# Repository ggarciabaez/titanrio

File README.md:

# titanrio
A RoboRIO-Inspired Expansion board for Robotics. Mostly for funsies + learning.

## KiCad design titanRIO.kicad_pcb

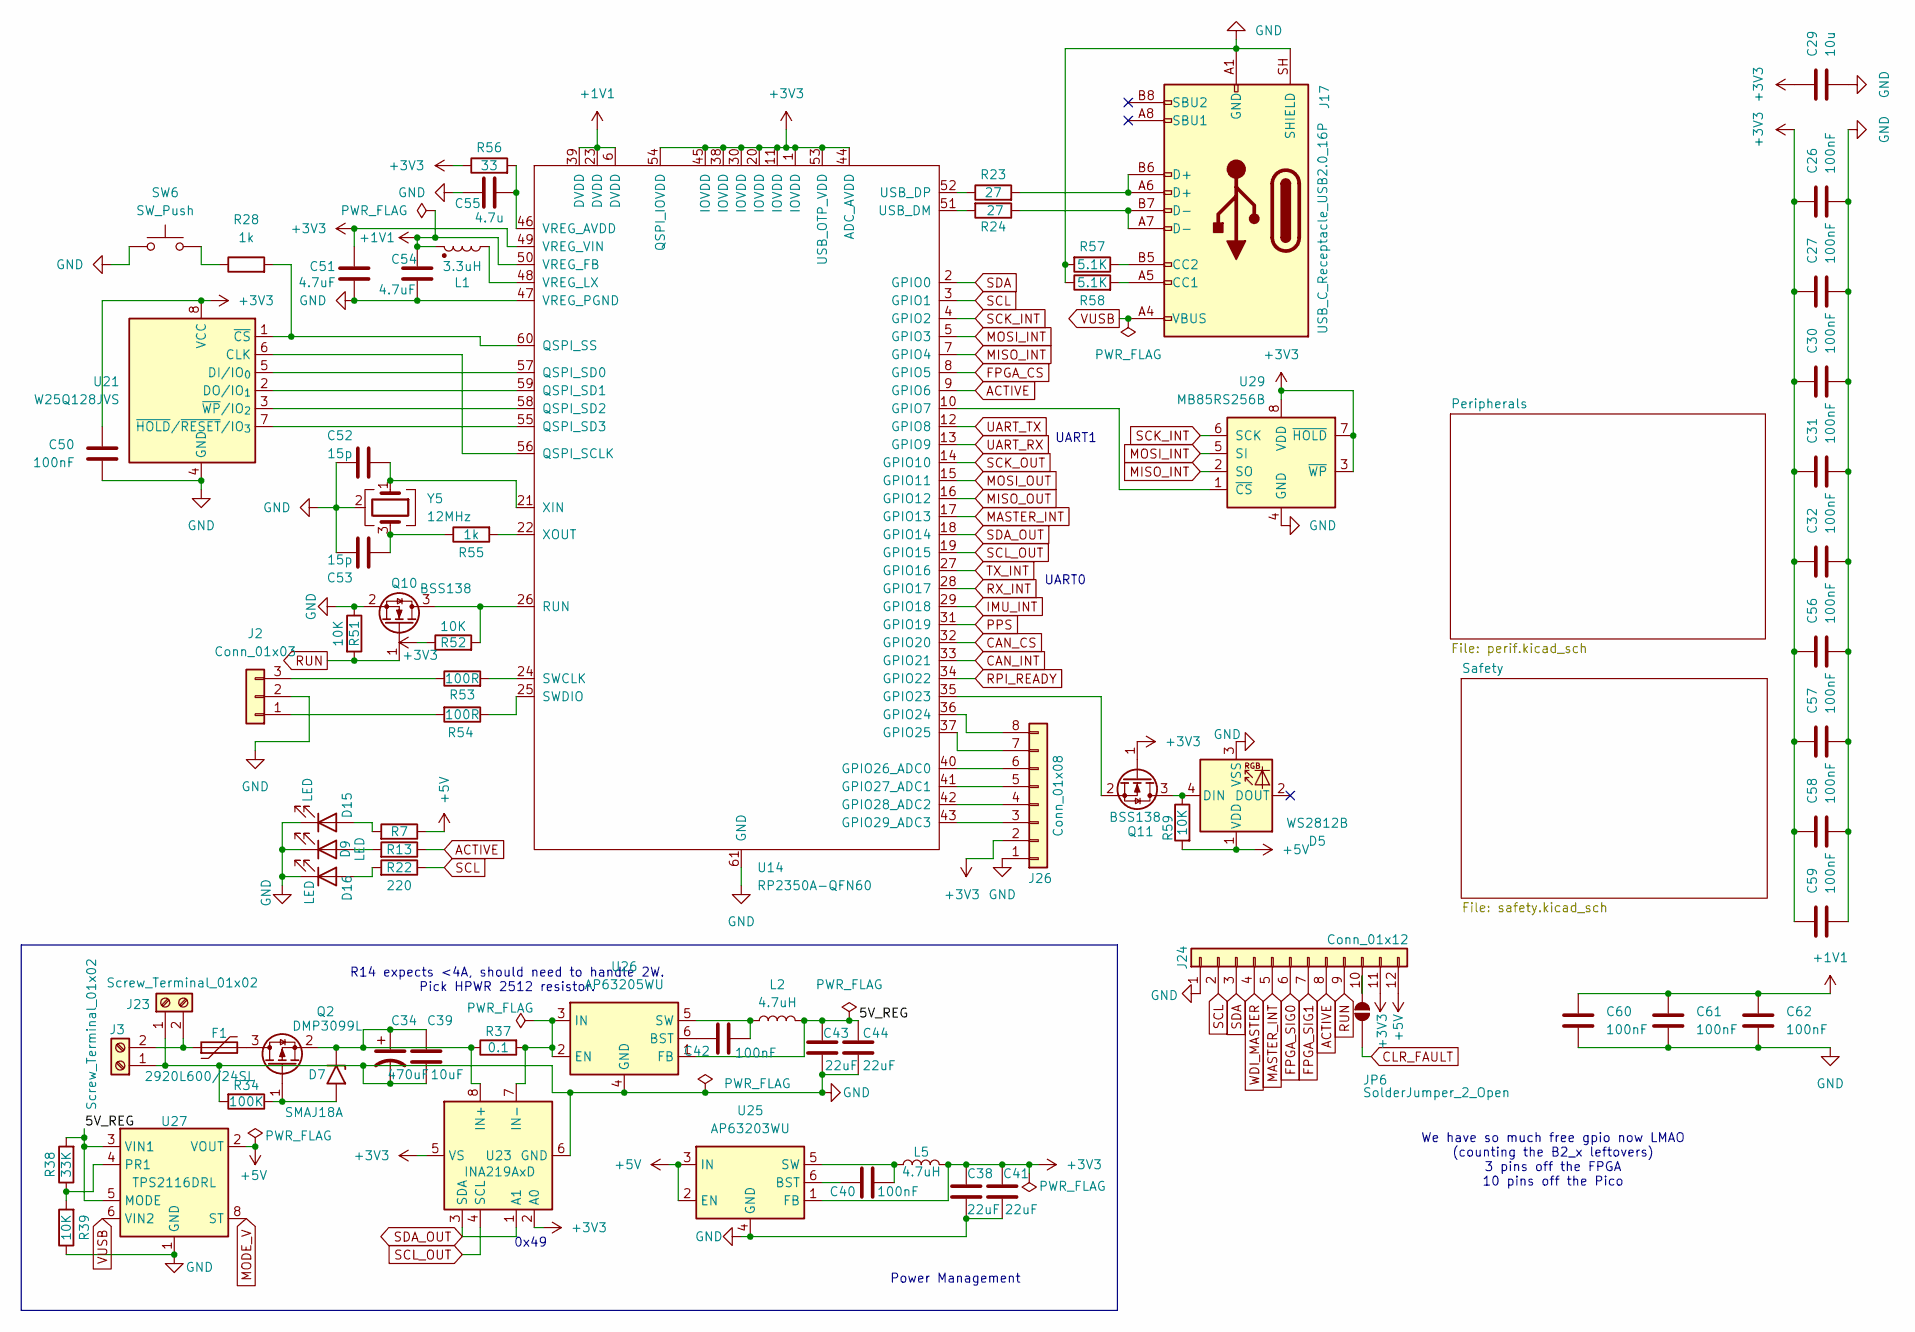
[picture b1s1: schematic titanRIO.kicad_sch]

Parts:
C26, C27, C30, C31, C32, C56, C57, C58, C59, C60, C61, C62: 100nF; C_0201_0603Metric
C29: 10u; C_0402_1005Metric
C34: 470uF; CP_Elec_8x10
C38, C41, C43, C44: 22uF; C_0603_1608Metric
C39: 10uF; C_0805_2012Metric
C40, C42: 100nF; C_0603_1608Metric
C50: 100nF; C_0402_1005Metric
C51, C54: 4.7uF; C_0402_1005Metric
C52, C53: 15p; C_0402_1005Metric
C55: 4.7u; C_0402_1005Metric
D5: WS2812B; LED_WS2812B_PLCC4_5.0x5.0mm_P3.2mm
D7: SMAJ18A; D_SMA
D9, D15, D16: LED; LED_1206_3216Metric
F1: 2920L600/24SL; Fuse_2920_7451Metric
J2: Conn_01x03; JST_XH_B3B-XH-AM_1x03_P2.50mm_Vertical
J3, J23: Screw_Terminal_01x02; TerminalBlock_Phoenix_MPT-0,5-2-2.54_1x02_P2.54mm_Horizontal
J17: USB_C_Receptacle_USB2.0_16P; USB_C_Receptacle_GCT_USB4105-xx-A_16P_TopMnt_Horizontal
J24: Conn_01x12; JST_GH_BM12B-GHS-TBT_1x12-1MP_P1.25mm_Vertical
J26: Conn_01x08; JST_GH_BM08B-GHS-TBT_1x08-1MP_P1.25mm_Vertical
JP6: SolderJumper_2_Open; SolderJumper-2_P1.3mm_Open_TrianglePad1.0x1.5mm
L1: 3.3uH; L_0805_2012Metric_Pad1.05x1.20mm_HandSolder
L2, L5: 4.7uH; L_0805_2012Metric
Q2: DMP3099L; SOT-23
Q10, Q11: BSS138; SOT-23
R7, R13, R22: 220; R_0805_2012Metric_Pad1.20x1.40mm_HandSolder
R23, R24: 27; R_0402_1005Metric
R28, R55: 1k; R_0402_1005Metric
R34: 100K; R_0402_1005Metric
R37: 0.1; R_2816_7142Metric_Pad3.20x4.45mm_HandSolder
R38: 33K; R_0402_1005Metric
R39: 10K; R_0402_1005Metric
R51, R52, R59: 10K; R_0603_1608Metric_Pad0.98x0.95mm_HandSolder
R53, R54: 100R; R_0402_1005Metric_Pad0.72x0.64mm_HandSolder
R56: 33; R_0402_1005Metric
R57, R58: 5.1K; R_0402_1005Metric
SW6: SW_Push; SW_Push_1P1T_NO_CK_KMR2
U14: RP2350A-QFN60; QFN-60-1EP_7x7mm_P0.4mm_EP3.4x3.4mm
U21: W25Q128JVS; SOIC-8_5.3x5.3mm_P1.27mm
U23: INA219AxD; SOIC-8_3.9x4.9mm_P1.27mm
U25: AP63203WU; TSOT-23-6
U26: AP63205WU; TSOT-23-6
U27: TPS2116DRL; SOT-583-8
U29: MB85RS256B; SO-8_3.9x4.9mm_P1.27mm
Y5: 12MHz; Oscillator_SMD_Abracon_ASE-4Pin_3.2x2.5mm

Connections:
+1V1: C54.1, C60.1, C61.1, C62.1, L1.1, U14.6 (DVDD), U14.23 (DVDD), U14.39 (DVDD), U14.50 (VREG_FB)
+3V3: C26.1, C27.1, C29.1, C30.1, C31.1, C32.1, C38.1, C41.1, C50.2, C51.1, C56.1, C57.1, C58.1, C59.1, J24.11, J26.2, L5.2, Q11.1 (G), R52.1, R56.1, U14.1 (IOVDD), U14.11 (IOVDD), U14.20 (IOVDD), U14.30 (IOVDD), U14.38 (IOVDD), U14.44 (ADC_AVDD), U14.45 (IOVDD), U14.49 (VREG_VIN), U14.53 (USB_OTP_VDD), U14.54 (QSPI_IOVDD), U21.8 (VCC), U23.2 (A0), U23.5 (VS), U25.1 (FB), U29.3 (~WP), U29.7 (~HOLD), U29.8 (VDD); also elsewhere on the board
+5V: D5.1 (VDD), J24.12, R7.1, R59.2, U25.2 (EN), U25.3 (IN), U27.2 (VOUT), U27.7 (VOUT); also elsewhere on the board
/5V_REG: C43.1, C44.1, L2.2, R38.2, U26.1 (FB), U27.3 (VIN1), U27.5 (MODE)
ACTIVE: J24.8, R13.1, U14.9 (GPIO6); also elsewhere on the board
CAN_CS: U14.32 (GPIO20); also elsewhere on the board
CAN_INT: U14.33 (GPIO21); also elsewhere on the board
CLR_FAULT: JP6.1 (A); also elsewhere on the board
FPGA_CS: U14.8 (GPIO5); also elsewhere on the board
FPGA_SIG0: J24.6; also elsewhere on the board
FPGA_SIG1: J24.7; also elsewhere on the board
GND: C26.2, C27.2, C29.2, C30.2, C31.2, C32.2, C34.2, C38.2, C39.2, C41.2, C43.2, C44.2, C50.1, C51.2, C52.1, C53.1, C54.2, C55.1, C56.2, C57.2, C58.2, C59.2, C60.2, C61.2, C62.2, D5.3 (VSS), D9.1 (K), D15.1 (K), D16.1 (K), J2.2, J3.1, J17.A1 (GND), J17.A12 (GND), J17.B1 (GND), J17.B12 (GND), J17.SH (SHIELD), J23.1, J24.1, J26.1, Q10.2 (S), R34.2, R39.1, R51.1, R57.2, R58.1, SW6.1, U14.47 (VREG_PGND), U14.61 (GND), U21.4 (GND), U23.6 (GND), U25.4 (GND), U26.4 (GND), U27.1 (GND), U29.4 (GND), Y5.2 (G), Y5.4 (G); also elsewhere on the board
IMU_INT: U14.29 (GPIO18); also elsewhere on the board
MASTER_INT: J24.5, U14.17 (GPIO13)
MISO_INT: U14.7 (GPIO4), U29.2 (SO); also elsewhere on the board
MISO_OUT: U14.16 (GPIO12); also elsewhere on the board
MODE_V: U27.8 (ST)
MOSI_INT: U14.5 (GPIO3), U29.5 (SI); also elsewhere on the board
MOSI_OUT: U14.15 (GPIO11); also elsewhere on the board
unnamed: C53.2, R55.1, Y5.3
unnamed: D5.4 (DIN), Q11.3 (D), R59.1
unnamed: C34.1, C39.1, D7.1 (A1), Q2.2 (S), R37.1, U23.8 (IN+)
unnamed: D7.2 (A2), Q2.1 (G), R34.1
unnamed: D9.2 (A), R13.2
unnamed: D15.2 (A), R7.2
unnamed: D16.2 (A), R22.2
unnamed: J2.1, R54.2
unnamed: J2.3, R53.1
unnamed: J17.A5 (CC1), R58.2
unnamed: J17.B5 (CC2), R57.1
unnamed: J17.A6 (D+), J17.B6 (D+), R23.2
unnamed: J17.A7 (D-), J17.B7 (D-), R24.1
unnamed: F1.1, J3.2, J23.2
unnamed: J24.10, JP6.2 (B)
unnamed: J26.3, U14.43 (GPIO29_ADC3)
unnamed: J26.4, U14.42 (GPIO28_ADC2)
unnamed: J26.5, U14.41 (GPIO27_ADC1)
unnamed: J26.6, U14.40 (GPIO26_ADC0)
unnamed: J26.7, U14.37 (GPIO25)
unnamed: J26.8, U14.36 (GPIO24)
unnamed: F1.2, Q2.3 (D)
unnamed: Q10.3 (D), R52.2, U14.26 (RUN)
unnamed: Q11.2 (S), U14.35 (GPIO23)
unnamed: R28.1, SW6.2
unnamed: U14.10 (GPIO7), U29.1 (~CS)
unnamed: U14.56 (QSPI_SCLK), U21.6 (CLK)
unnamed: U14.57 (QSPI_SD0), U21.5 (DI/IO_{0})
unnamed: U14.59 (QSPI_SD1), U21.2 (DO/IO_{1})
unnamed: U14.58 (QSPI_SD2), U21.3 (~WP/IO_{2})
unnamed: U14.55 (QSPI_SD3), U21.7 (~HOLD/~RESET/IO_{3})
unnamed: R28.2, U14.60 (QSPI_SS), U21.1 (~CS)
unnamed: R53.2, U14.24 (SWCLK)
unnamed: R54.1, U14.25 (SWDIO)
unnamed: R24.2, U14.51 (USB_DM)
unnamed: R23.1, U14.52 (USB_DP)
unnamed: C55.2, R56.2, U14.46 (VREG_AVDD)
unnamed: L1.2, U14.48 (VREG_LX)
unnamed: C52.2, U14.21 (XIN), Y5.1
unnamed: R55.2, U14.22 (XOUT)
unnamed: R37.2, U23.7 (IN-), U26.2 (EN), U26.3 (IN)
unnamed: C40.1, U25.6 (BST)
unnamed: C40.2, L5.1, U25.5 (SW)
unnamed: C42.1, U26.6 (BST)
unnamed: C42.2, L2.1, U26.5 (SW)
unnamed: R38.1, R39.2, U27.4 (PR1)
PPS: U14.31 (GPIO19); also elsewhere on the board
RPI_READY: U14.34 (GPIO22); also elsewhere on the board
RUN: J24.9, Q10.1 (G), R51.2
RX_INT: U14.28 (GPIO17); also elsewhere on the board
SCK_INT: U14.4 (GPIO2), U29.6 (SCK); also elsewhere on the board
SCK_OUT: U14.14 (GPIO10); also elsewhere on the board
SCL: J24.2, R22.1, U14.3 (GPIO1)
SCL_OUT: U14.19 (GPIO15), U23.4 (SCL); also elsewhere on the board
SDA: J24.3, U14.2 (GPIO0)
SDA_OUT: U14.18 (GPIO14), U23.1 (A1), U23.3 (SDA); also elsewhere on the board
TX_INT: U14.27 (GPIO16); also elsewhere on the board
UART_RX: U14.13 (GPIO9); also elsewhere on the board
UART_TX: U14.12 (GPIO8); also elsewhere on the board
VUSB: J17.A4 (VBUS), J17.A9 (VBUS), J17.B4 (VBUS), J17.B9 (VBUS), U27.6 (VIN2)
WDI_MASTER: J24.4; also elsewhere on the board

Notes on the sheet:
0x49
We have so much free gpio now LMAO (counting the B2_x leftovers) 3 pins off the FPGA 10 pins off the Pico
R14 expects <4A, should need to handle 2W. Pick HPWR 2512 resistor.
UART0
Power Management
UART1

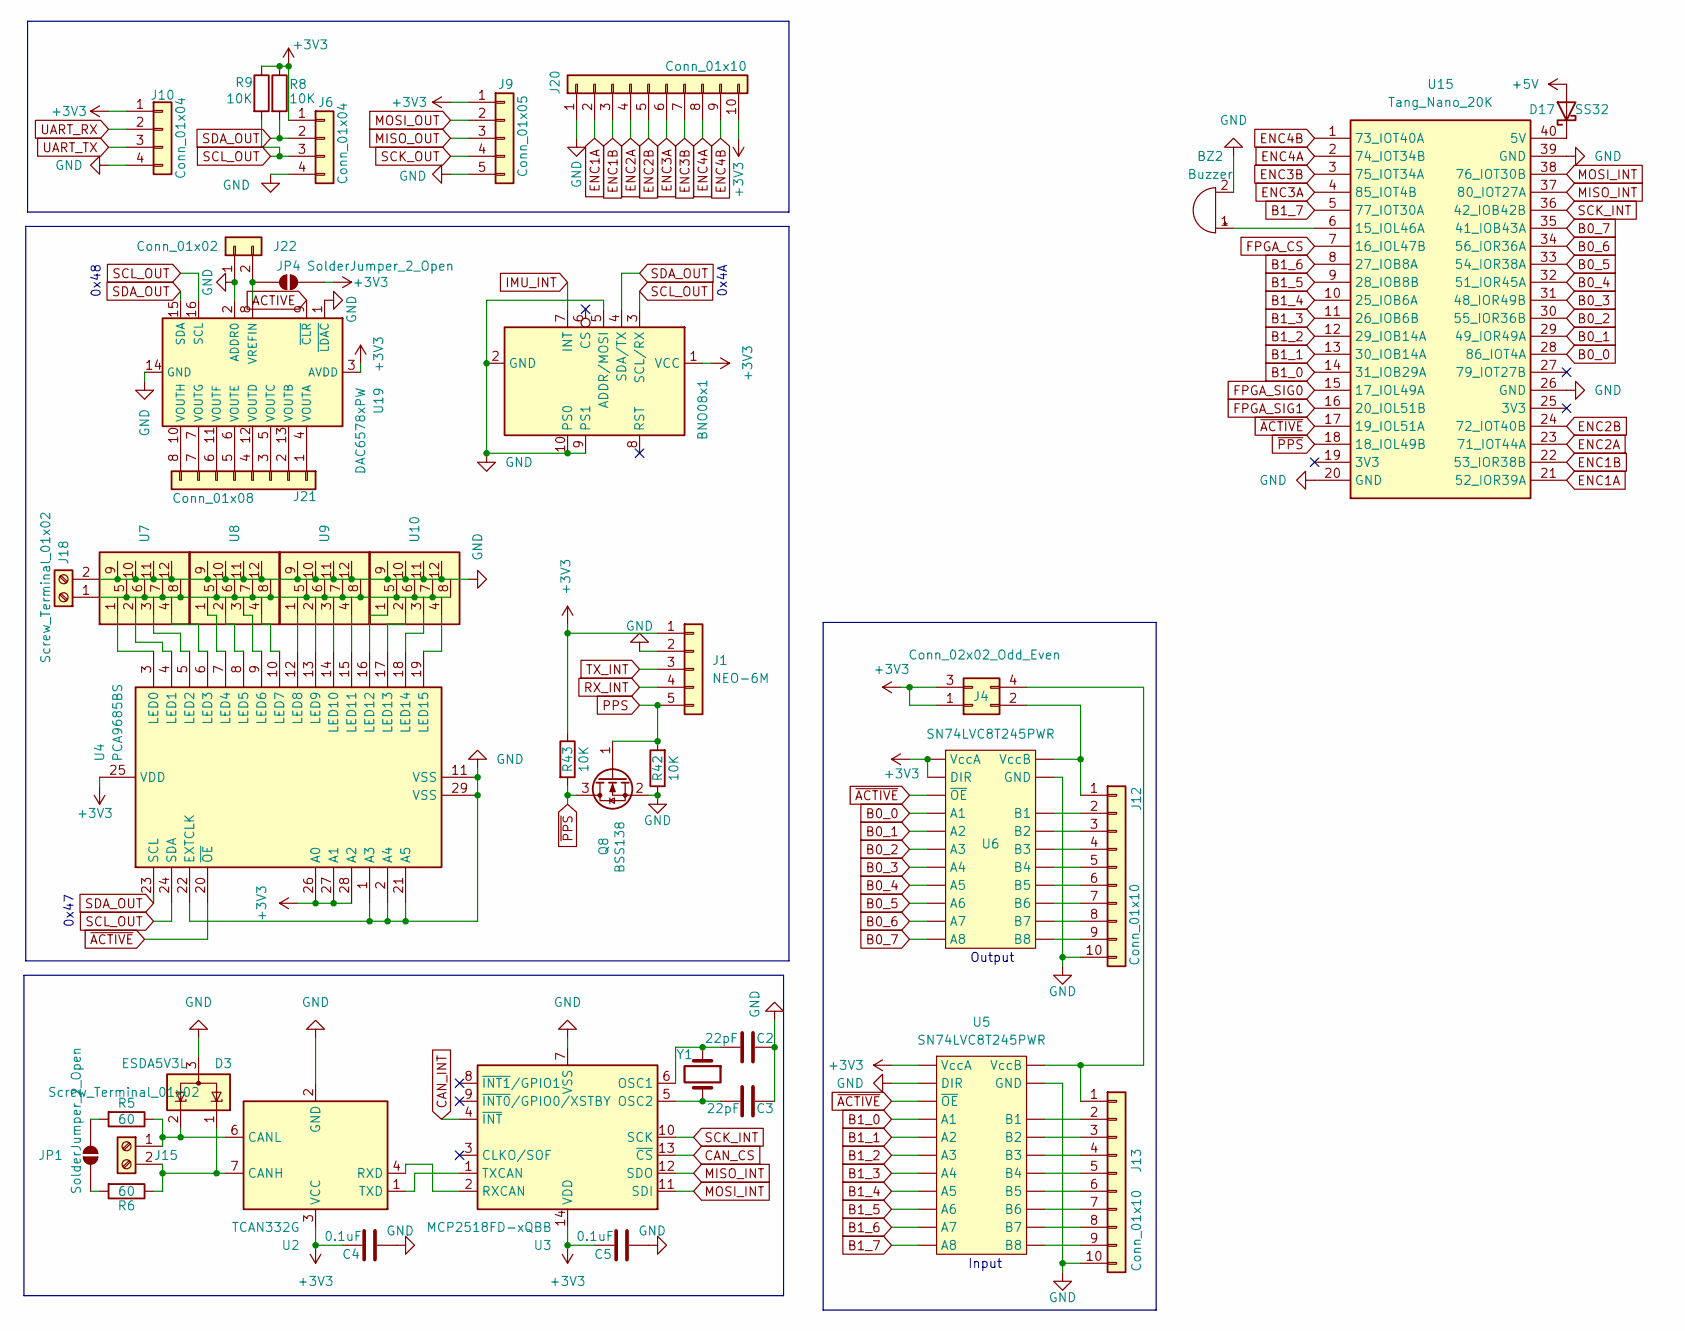
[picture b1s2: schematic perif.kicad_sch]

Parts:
BNO08x1: PinSocket_1x10_P2.54mm_Vertical
BZ2: Buzzer; Buzzer_12x9.5RM7.6
C2, C3: 22pF; C_0402_1005Metric_Pad0.74x0.62mm_HandSolder
C4, C5: 0.1uF; C_0402_1005Metric_Pad0.74x0.62mm_HandSolder
D3: ESDA5V3L; SOT-23-3
D17: SS32; D_SMA
J1: NEO-6M; PinSocket_1x05_P2.54mm_Vertical
J4: Conn_02x02_Odd_Even; PinHeader_2x02_P2.54mm_Vertical
J6, J10: Conn_01x04; JST_GH_BM04B-GHS-TBT_1x04-1MP_P1.25mm_Vertical
J9: Conn_01x05; JST_GH_BM05B-GHS-TBT_1x05-1MP_P1.25mm_Vertical
J12, J13, J20: Conn_01x10; JST_GH_BM10B-GHS-TBT_1x10-1MP_P1.25mm_Vertical
J15, J18: Screw_Terminal_01x02; TerminalBlock_Phoenix_MPT-0,5-2-2.54_1x02_P2.54mm_Horizontal
J21: Conn_01x08; JST_GH_BM08B-GHS-TBT_1x08-1MP_P1.25mm_Vertical
J22: Conn_01x02; JST_PH_B2B-PH-K_1x02_P2.00mm_Vertical
JP1, JP4: SolderJumper_2_Open; SolderJumper-2_P1.3mm_Open_TrianglePad1.0x1.5mm
Q8: BSS138; SOT-23
R5: 60; R_1812_4532Metric
R6: 60; R_1812_4532Metric_Pad1.30x3.40mm_HandSolder
R8, R9, R42, R43: 10K; R_0603_1608Metric_Pad0.98x0.95mm_HandSolder
U2: TCAN332G; TSOT-23-8
U3: MCP2518FD-xQBB; DFN-14-1EP_3x4.5mm_P0.65mm_EP1.65x4.25mm
U4: PCA9685BS; QFN-28-1EP_6x6mm_P0.65mm_EP4.25x4.25mm
U5, U6: SN74LVC8T245PWR; TSSOP-24_TI-PW; LCSC C27643
U7, U8, U9, U10: PinHeader_3x4_P2.54mm_Vertical
U15: Tang_Nano_20K; DIP-40_TangNano20K
U19: DAC6578xPW; TSSOP-16_4.4x5mm_P0.65mm
Y1: 20mHz; L_1008_2520Metric_Pad1.43x2.20mm_HandSolder

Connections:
+3V3: BNO08x1.1 (VCC), C4.2, C5.2, J1.1, J4.1, J4.3, J6.1, J9.1, J10.1, J20.10, JP4.1 (A), R8.1, R9.1, R43.1, U2.3 (VCC), U3.14 (VDD), U4.25 (VDD), U4.26 (A0), U4.27 (A1), U4.28 (A2), U5.1 (VccA), U6.1 (VccA), U6.2 (DIR), U19.3 (AVDD); also elsewhere on the board
+5V: D17.2 (A); also elsewhere on the board
ACTIVE: U19.9 (~CLR); also elsewhere on the board
B0_0: U6.3 (A1), U15.28 (86_IOT4A)
B0_1: U6.4 (A2), U15.29 (49_IOR49A)
B0_2: U6.5 (A3), U15.30 (55_IOR36B)
B0_3: U6.6 (A4), U15.31 (48_IOR49B)
B0_4: U6.7 (A5), U15.32 (51_IOR45A)
B0_5: U6.8 (A6), U15.33 (54_IOR38A)
B0_6: U6.9 (A7), U15.34 (56_IOR36A)
B0_7: U6.10 (A8), U15.35 (41_IOB43A)
B1_0: U5.3 (A1), U15.14 (31_IOB29A)
B1_1: U5.4 (A2), U15.13 (30_IOB14A)
B1_2: U5.5 (A3), U15.12 (29_IOB14A)
B1_3: U5.6 (A4), U15.11 (26_IOB6B)
B1_4: U5.7 (A5), U15.10 (25_IOB6A)
B1_5: U5.8 (A6), U15.9 (28_IOB8B)
B1_6: U5.9 (A7), U15.8 (27_IOB8A)
B1_7: U5.10 (A8), U15.5 (77_IOT30A)
CAN_CS: U3.13 (~CS); also elsewhere on the board
CAN_INT: U3.4 (~INT); also elsewhere on the board
ENC1A: J20.2, U15.21 (52_IOR39A)
ENC1B: J20.3, U15.22 (53_IOR38B)
ENC2A: J20.4, U15.23 (71_IOT44A)
ENC2B: J20.5, U15.24 (72_IOT40B)
ENC3A: J20.6, U15.4 (85_IOT4B)
ENC3B: J20.7, U15.3 (75_IOT34A)
ENC4A: J20.8, U15.2 (74_IOT34B)
ENC4B: J20.9, U15.1 (73_IOT40A)
FPGA_CS: U15.7 (16_IOL47B); also elsewhere on the board
FPGA_SIG0: U15.15 (17_IOL49A); also elsewhere on the board
FPGA_SIG1: U15.16 (20_IOL51B); also elsewhere on the board
GND: BNO08x1.2 (GND), BNO08x1.5 (ADDR/MOSI), BNO08x1.9 (PS1), BNO08x1.10 (PS0), BZ2.2 (-), C2.1, C3.1, C4.1, C5.1, D3.3 (A), J1.2, J6.4, J9.5, J10.4, J12.10, J13.10, J18.2, J20.1, J22.1, Q8.2 (S), R42.1, U2.2 (GND), U3.7 (VSS), U3.15 (VSS), U4.1 (A3), U4.2 (A4), U4.11 (VSS), U4.21 (A5), U4.22 (EXTCLK), U4.29 (VSS), U5.2 (DIR), U5.11 (GND), U5.12 (GND), U5.13 (GND), U6.11 (GND), U6.12 (GND), U6.13 (GND), U7.9, U7.10, U7.11, U7.12, U8.9, U8.10, U8.11, U8.12, U9.9, U9.10, U9.11, U9.12, U10.9, U10.10, U10.11, U10.12, U15.20 (GND), U15.26 (GND), U15.39 (GND), U19.1 (~LDAC), U19.2 (ADDR0), U19.14 (GND); also elsewhere on the board
IMU_INT: BNO08x1.7 (INT); also elsewhere on the board
MISO_INT: U3.12 (SDO), U15.37 (80_IOT27A); also elsewhere on the board
MISO_OUT: J9.3; also elsewhere on the board
MOSI_INT: U3.11 (SDI), U15.38 (76_IOT30B); also elsewhere on the board
MOSI_OUT: J9.2; also elsewhere on the board
unnamed: BZ2.1 (+), U15.6 (15_IOL46A)
unnamed: D17.1 (K), U15.40 (5V)
unnamed: J4.2, J12.1, U6.23 (VccB), U6.24 (VccB)
unnamed: J12.2, U6.21 (B1)
unnamed: J12.3, U6.20 (B2)
unnamed: J12.4, U6.19 (B3)
unnamed: J12.5, U6.18 (B4)
unnamed: J12.6, U6.17 (B5)
unnamed: J12.7, U6.16 (B6)
unnamed: J12.8, U6.15 (B7)
unnamed: J12.9, U6.14 (B8)
unnamed: J4.4, J13.1, U5.23 (VccB), U5.24 (VccB)
unnamed: J13.2, U5.21 (B1)
unnamed: J13.3, U5.20 (B2)
unnamed: J13.4, U5.19 (B3)
unnamed: J13.5, U5.18 (B4)
unnamed: J13.6, U5.17 (B5)
unnamed: J13.7, U5.16 (B6)
unnamed: J13.8, U5.15 (B7)
unnamed: J13.9, U5.14 (B8)
unnamed: D3.2 (K), J15.1, R5.1, U2.6 (CANL)
unnamed: D3.1 (K), J15.2, R6.1, U2.7 (CANH)
unnamed: J18.1, U7.5, U7.6, U7.7, U7.8, U8.5, U8.6, U8.7, U8.8, U9.5, U9.6, U9.7, U9.8, U10.5, U10.6, U10.7, U10.8
unnamed: J21.1, U19.4 (VOUTA)
unnamed: J21.2, U19.13 (VOUTB)
unnamed: J21.3, U19.5 (VOUTC)
unnamed: J21.4, U19.12 (VOUTD)
unnamed: J21.5, U19.6 (VOUTE)
unnamed: J21.6, U19.11 (VOUTF)
unnamed: J21.7, U19.7 (VOUTG)
unnamed: J21.8, U19.10 (VOUTH)
unnamed: J22.2, JP4.2 (B), U19.8 (VREFIN)
unnamed: JP1.1 (A), R5.2
unnamed: JP1.2 (B), R6.2
unnamed: U2.4 (RXD), U3.2 (RXCAN)
unnamed: U2.1 (TXD), U3.1 (TXCAN)
unnamed: C2.2, U3.6 (OSC1), Y1.1
unnamed: C3.2, U3.5 (OSC2), Y1.2
unnamed: U4.3 (LED0), U7.1
unnamed: U4.4 (LED1), U7.2
unnamed: U4.5 (LED2), U7.3
unnamed: U4.6 (LED3), U7.4
unnamed: U4.7 (LED4), U8.1
unnamed: U4.8 (LED5), U8.2
unnamed: U4.9 (LED6), U8.3
unnamed: U4.10 (LED7), U8.4
unnamed: U4.12 (LED8), U9.1
unnamed: U4.13 (LED9), U9.2
unnamed: U4.14 (LED10), U9.3
unnamed: U4.15 (LED11), U9.4
unnamed: U4.16 (LED12), U10.1
unnamed: U4.17 (LED13), U10.2
unnamed: U4.18 (LED14), U10.3
unnamed: U4.19 (LED15), U10.4
PPS: J1.5, Q8.1 (G), R42.2; also elsewhere on the board
RX_INT: J1.4; also elsewhere on the board
SCK_INT: U3.10 (SCK), U15.36 (42_IOB42B); also elsewhere on the board
SCK_OUT: J9.4; also elsewhere on the board
SCL_OUT: BNO08x1.3 (SCL/RX), J6.3, R9.2, U4.24 (SDA), U19.16 (SCL); also elsewhere on the board
SDA_OUT: BNO08x1.4 (SDA/TX), J6.2, R8.2, U4.23 (SCL), U19.15 (SDA); also elsewhere on the board
TX_INT: J1.3; also elsewhere on the board
UART_RX: J10.2; also elsewhere on the board
UART_TX: J10.3; also elsewhere on the board
~ACTIVE: U4.20 (~OE), U5.22 (~OE), U6.22 (~OE), U15.17 (19_IOL51A); also elsewhere on the board
~PPS: Q8.3 (D), R43.2, U15.18 (18_IOL49B)

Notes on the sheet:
0x47
Input
0x48
Output
0x4A

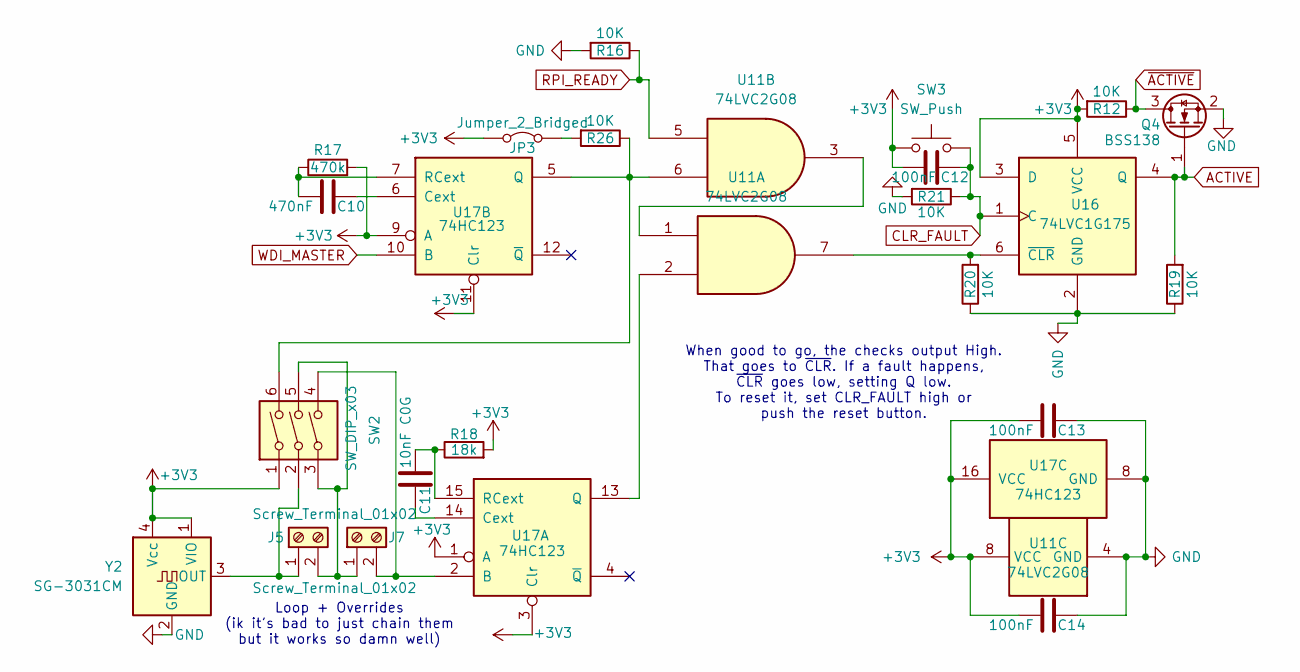
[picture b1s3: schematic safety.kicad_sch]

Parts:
C10: 470nF; C_0603_1608Metric
C11: 10nF C0G; C_0603_1608Metric_Pad1.08x0.95mm_HandSolder
C12, C13, C14: 100nF; C_0402_1005Metric_Pad0.74x0.62mm_HandSolder
J5, J7: Screw_Terminal_01x02; TerminalBlock_Phoenix_MPT-0,5-2-2.54_1x02_P2.54mm_Horizontal
JP3: Jumper_2_Bridged; PinHeader_1x2_P2.54mm_Vertical
Q4: BSS138; SOT-23
R12, R16, R19, R20, R21, R26: 10K; R_0603_1608Metric_Pad0.98x0.95mm_HandSolder
R17: 470k; R_0603_1608Metric_Pad0.98x0.95mm_HandSolder
R18: 18k; R_0603_1608Metric_Pad0.98x0.95mm_HandSolder
SW2: SW_DIP_x03; SW_DIP_SPSTx03_Slide_9.78x9.8mm_W8.61mm_P2.54mm
SW3: SW_Push; SW_Push_1P1T_NO_CK_KMR2
U11: 74LVC2G08; VSSOP-8_2.3x2mm_P0.5mm
U16: 74LVC1G175; SOT-23-6_Handsoldering
U17: 74HC123; SOP-16_4.4x10.4mm_P1.27mm
Y2: SG-3031CM; Oscillator_SMD_SeikoEpson_SG3030CM

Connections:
+3V3: C12.2, C13.2, C14.2, JP3.1 (A), R12.2, R17.2, R18.2, SW2.1, SW3.1, U11.8 (VCC), U16.3 (D), U16.5 (VCC), U17.1 (A), U17.3 (Clr), U17.9 (A), U17.11 (Clr), U17.16 (VCC), Y2.1 (VIO), Y2.4 (Vcc); also elsewhere on the board
ACTIVE: Q4.1 (G), R19.2, U16.4 (Q); also elsewhere on the board
CLR_FAULT: C12.1, R21.1, SW3.2, U16.1 (C); also elsewhere on the board
GND: C13.1, C14.1, Q4.2 (S), R16.2, R19.1, R20.1, R21.2, U11.4 (GND), U16.2 (GND), U17.8 (GND), Y2.2 (GND); also elsewhere on the board
unnamed: J5.1, SW2.2, Y2.3 (OUT)
unnamed: J5.2, J7.1, SW2.3, SW2.5
unnamed: J7.2, SW2.4, U17.2 (B)
unnamed: JP3.2 (B), R26.2
unnamed: U11.1, U11.3
unnamed: R20.2, U11.7, U16.6 (~CLR)
unnamed: C11.1, U17.14 (Cext)
unnamed: U11.2, U17.13 (Q)
unnamed: C11.2, R18.1, U17.15 (RCext)
unnamed: C10.1, U17.6 (Cext)
unnamed: R26.1, SW2.6, U11.6, U17.5 (Q)
unnamed: C10.2, R17.1, U17.7 (RCext)
RPI_READY: R16.1, U11.5; also elsewhere on the board
WDI_MASTER: U17.10 (B); also elsewhere on the board
~ACTIVE: Q4.3 (D), R12.1; also elsewhere on the board

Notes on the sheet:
When good to go, the checks output High. That goes to ~{CLR}. If a fault happens, ~{CLR} goes low, setting Q low. To reset it, set CLR_FAULT high or push the reset button.
Loop + Overrides (ik it's bad to just chain them but it works so damn well)

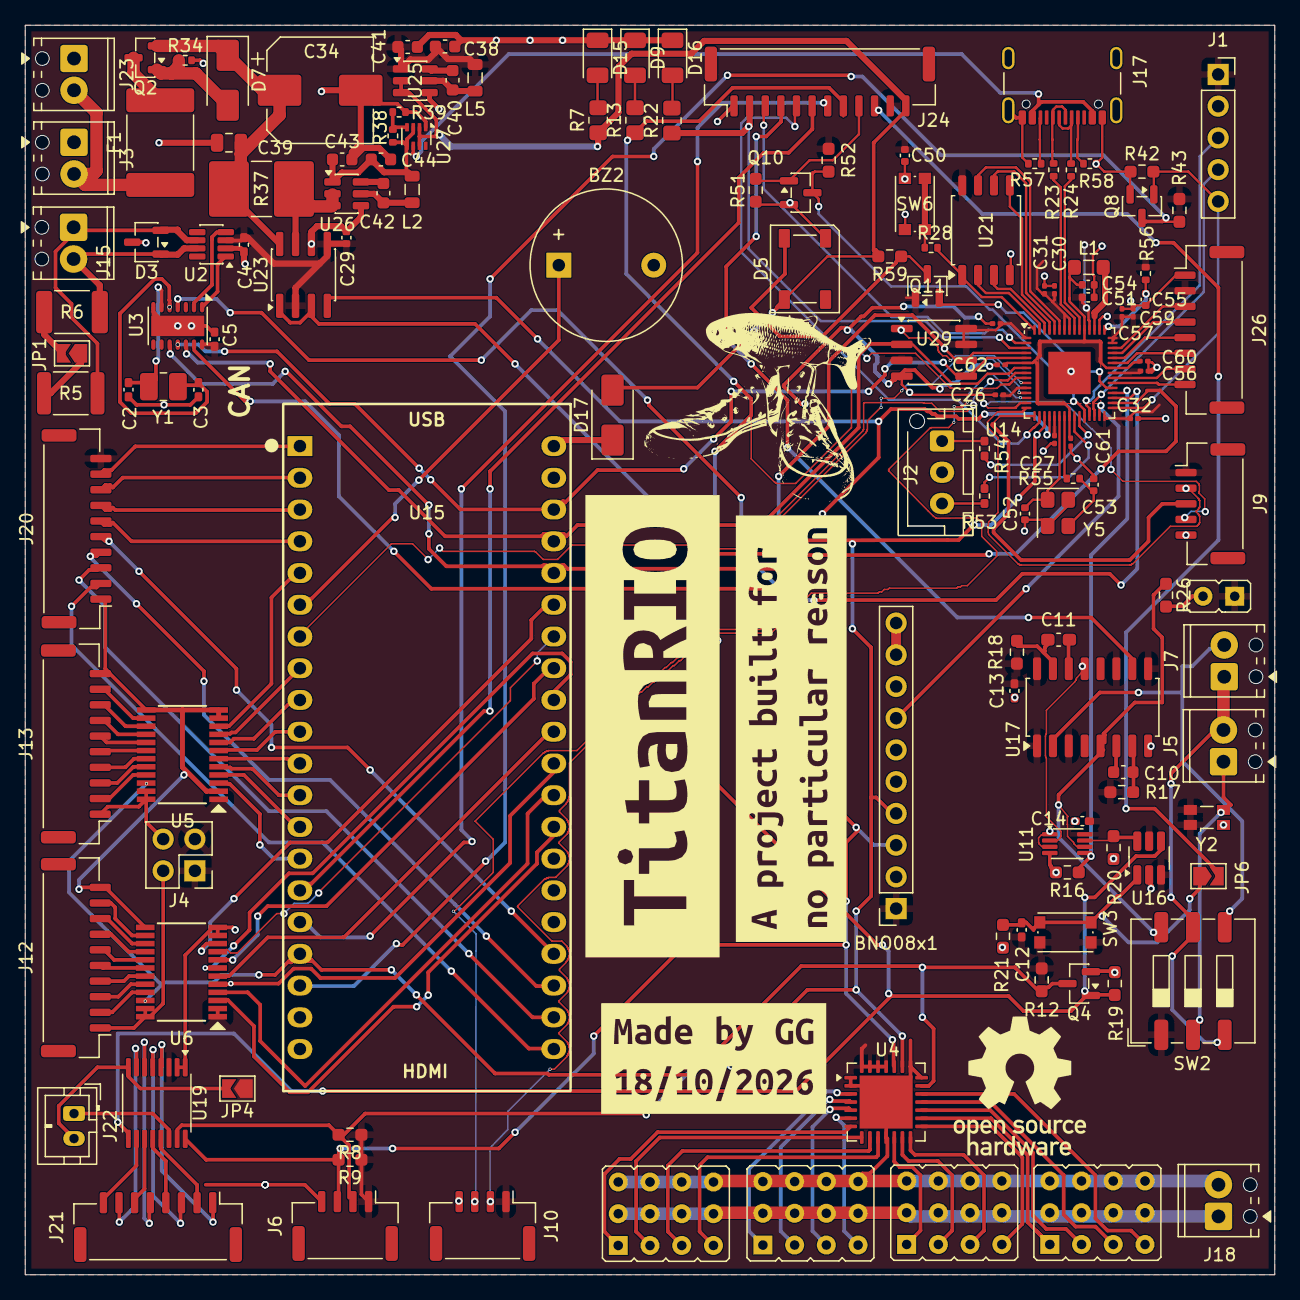
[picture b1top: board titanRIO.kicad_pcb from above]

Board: 2 copper layers, 100.0 x 100.0 mm, 141 parts (0 on the bottom side), 171 nets.

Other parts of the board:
kibuzzard-6AD48C4E: G***; kibuzzard-6AD48C4E
kibuzzard-6AD48C9F: G***; kibuzzard-6AD48C9F
kibuzzard-6AD48C85: G***; kibuzzard-6AD48C85

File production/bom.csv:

Designator,Footprint,Quantity,Value,LCSC Part #
BNO08X1,PinSocket_1x10_P2.54mm_Vertical,1,~,
BZ2,Buzzer_12x9.5RM7.6,1,Buzzer,
C10,0603,1,470nF,
C11,0603,1,10nF C0G,
"C12, C13, C14, C50",0402,4,100nF,
"C2, C3",0402,2,22pF,
"C26, C27, C30, C31, C32, C56, C57, C58, C59, C60, C61, C62",0201,12,100nF,
C29,0402,1,10u,
C34,CP_Elec_8x10,1,470uF,
"C38, C41, C43, C44",0603,4,22uF,
C39,0805,1,10uF,
"C4, C5",0402,2,0.1uF,
"C40, C42",0603,2,100nF,
"C51, C54",0402,2,4.7uF,
"C52, C53",0402,2,15p,
C55,0402,1,4.7u,
"D15, D16, D9",1206,3,LED,
D17,D_SMA,1,SS32,
D3,SOT-23-3,1,ESDA5V3L,
D5,LED_WS2812B_PLCC4_5.0x5.0mm_P3.2mm,1,WS2812B,
D7,D_SMA,1,SMAJ18A,
F1,2920,1,2920L600/24SL,
J1,PinSocket_1x05_P2.54mm_Vertical,1,NEO-6M,
"J10, J6",JST_GH_BM04B-GHS-TBT_1x04-1MP_P1.25mm_Vertical,2,Conn_01x04,
"J12, J13, J20",JST_GH_BM10B-GHS-TBT_1x10-1MP_P1.25mm_Vertical,3,Conn_01x10,
"J15, J18, J23, J3, J5, J7","TerminalBlock_Phoenix_MPT-0,5-2-2.54_1x02_P2.54mm_Horizontal",6,Screw_Terminal_01x02,
J17,USB_C_Receptacle_GCT_USB4105-xx-A_16P_TopMnt_Horizontal,1,USB_C_Receptacle_USB2.0_16P,
J2,JST_XH_B3B-XH-AM_1x03_P2.50mm_Vertical,1,Conn_01x03,
"J21, J26",JST_GH_BM08B-GHS-TBT_1x08-1MP_P1.25mm_Vertical,2,Conn_01x08,
J22,JST_PH_B2B-PH-K_1x02_P2.00mm_Vertical,1,Conn_01x02,
J24,JST_GH_BM12B-GHS-TBT_1x12-1MP_P1.25mm_Vertical,1,Conn_01x12,
J4,PinHeader_2x02_P2.54mm_Vertical,1,Conn_02x02_Odd_Even,
J9,JST_GH_BM05B-GHS-TBT_1x05-1MP_P1.25mm_Vertical,1,Conn_01x05,
JP3,PinHeader_1x2_P2.54mm_Vertical,1,Jumper_2_Bridged,
L1,0805,1,3.3uH,
"L2, L5",0805,2,4.7uH,
"Q10, Q11, Q4, Q8",SOT-23,4,BSS138,
Q2,SOT-23,1,DMP3099L,
"R12, R16, R19, R20, R21, R26, R42, R43, R51, R52, R59, R8, R9",0603,13,10K,
"R13, R22, R7",0805,3,220,
R17,0603,1,470k,
R18,0603,1,18k,
"R23, R24",0402,2,27,
"R28, R55",0402,2,1k,
R34,0402,1,100K,
R37,2816,1,0.1,
R38,0402,1,33K,
R39,0402,1,10K,
"R5, R6",1812,2,60,
"R53, R54",0402,2,100R,
R56,0402,1,33,
"R57, R58",0402,2,5.1K,
SW2,SW_DIP_SPSTx03_Slide_9.78x9.8mm_W8.61mm_P2.54mm,1,SW_DIP_x03,
"SW3, SW6",SW_Push_1P1T_NO_CK_KMR2,2,SW_Push,
"U10, U7, U8, U9",PinHeader_3x4_P2.54mm_Vertical,4,~,
U11,VSSOP-8_2.3x2mm_P0.5mm,1,74LVC2G08,
U14,QFN-60-1EP_7x7mm_P0.4mm_EP3.4x3.4mm,1,RP2350A-QFN60,
U15,DIP-40_TangNano20K,1,Tang_Nano_20K,
U16,SOT-23-6_Handsoldering,1,74LVC1G175,
U17,SOP-16_4.4x10.4mm_P1.27mm,1,74HC123,
U19,TSSOP-16_4.4x5mm_P0.65mm,1,DAC6578xPW,
U2,TSOT-23-8,1,TCAN332G,
U21,SOIC-8_5.3x5.3mm_P1.27mm,1,W25Q128JVS,
U23,SOIC-8_3.9x4.9mm_P1.27mm,1,INA219AxD,
U25,TSOT-23-6,1,AP63203WU,
U26,TSOT-23-6,1,AP63205WU,
U27,SOT-583-8,1,TPS2116DRL,
U29,SO-8_3.9x4.9mm_P1.27mm,1,MB85RS256B,
U3,DFN-14-1EP_3x4.5mm_P0.65mm_EP1.65x4.25mm,1,MCP2518FD-xQBB,
U4,QFN-28-1EP_6x6mm_P0.65mm_EP4.25x4.25mm,1,PCA9685BS,
"U5, U6",TSSOP-24_TI-PW,2,SN74LVC8T245PWR,C27643
Y1,1008,1,20mHz,
Y2,Oscillator_SMD_SeikoEpson_SG3030CM,1,SG-3031CM,
Y5,Oscillator_SMD_Abracon_ASE-4Pin_3.2x2.5mm,1,12MHz,
